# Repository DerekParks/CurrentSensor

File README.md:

Read a Non-invasive AC Current Sensor (SCT-013) hooked up to a adc (ADS1115) and a ESP-01. Then emit to mqtt. 
Saves wifi and mqtt creds to SPIFFS.
If wifi creds not found will go into AP mode.

# Links
https://www.savjee.be/2019/07/Home-Energy-Monitor-ESP32-CT-Sensor-Emonlib/

https://learn.openenergymonitor.org/electricity-monitoring/ct-sensors/how-to-build-an-arduino-energy-monitor-measuring-current-only?redirected=true

https://github.com/openenergymonitor/EmonLib

https://cdn-learn.adafruit.com/downloads/pdf/adafruit-4-channel-adc-breakouts.pdf

https://forum.mysensors.org/topic/4887/sct-013-030-to-measure-watt/3

http://www.sensingthecity.com/creating-a-non-invasive-current-sensor/

# Web server
https://github.com/Jorgen-VikingGod/ESP8266-WiFi-Relay-Async

# Board desgin links

## ESP01 I2C
https://simple-circuit.com/esp8266-esp-01-i2c-lcd/

## RST and FLASH switch
https://www.instructables.com/id/FTDI-ESP8266-Definitive-Wiring/

https://www.allaboutcircuits.com/projects/breadboard-and-program-an-esp-01-circuit-with-the-arduino-ide/

https://www.allaboutcircuits.com/projects/flashing-the-ESP-01-firmware-to-SDK-v2.0.0-is-easier-now/

https://taillieu.info/index.php/articles/category-list/204-esp8266-developer-board-for-the-esp-01-and-esp-12

## Used for FTDI:
https://github.com/ppelleti/avr-arduino-kicad

https://www.forward.com.au/pfod/ESP8266/GPIOpins/ESP8266_01_pin_magic.html

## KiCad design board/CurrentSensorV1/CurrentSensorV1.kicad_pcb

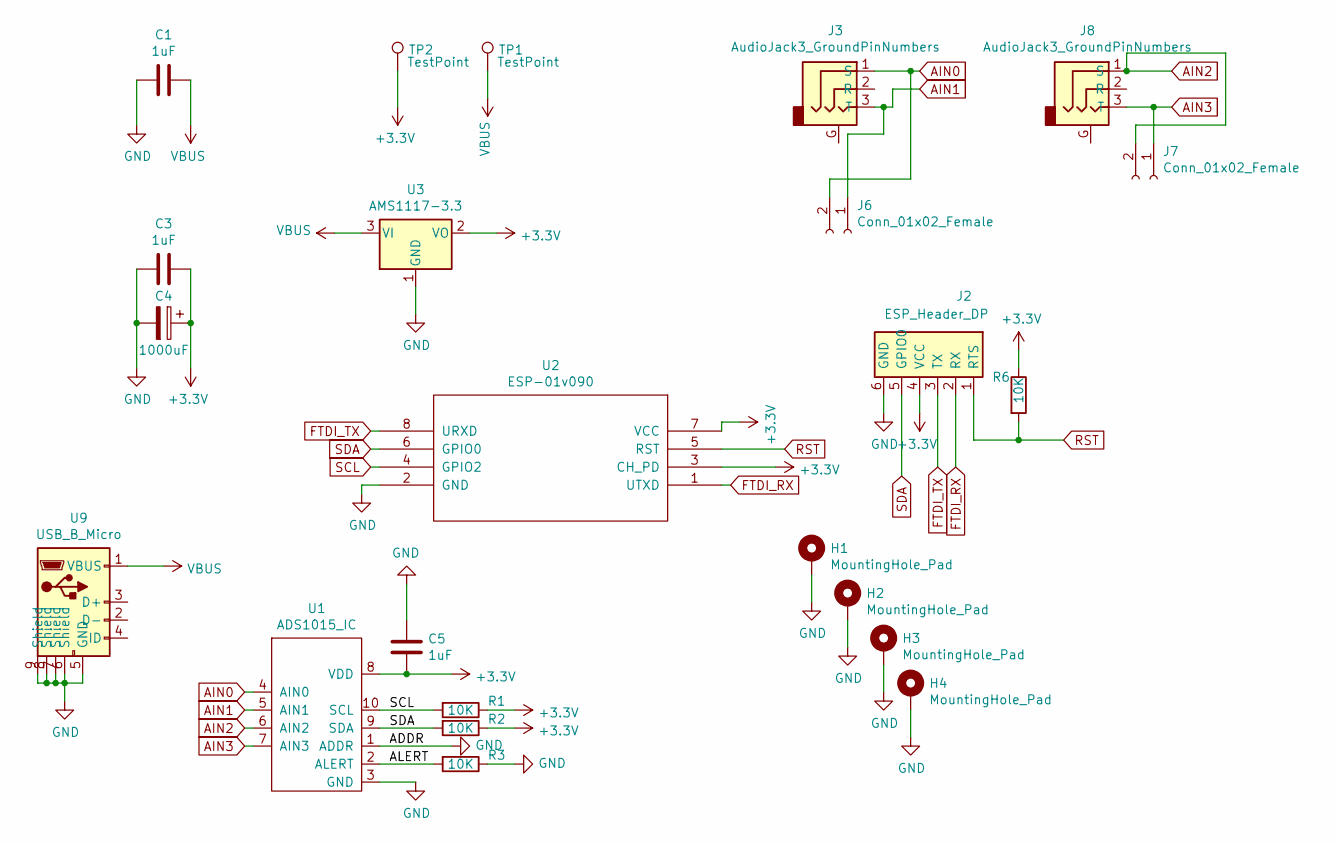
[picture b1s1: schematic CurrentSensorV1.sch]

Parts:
C1, C3, C5: 1uF; C_0402_1005Metric; LCSC C52923
C4: 1000uF; C_Elec_8x10.2; LCSC C99833
H1, H2, H3, H4: MountingHole_Pad; MountingHole_2.5mm_Pad
J2: ESP_Header_DP; FTDI_Header
J3, J8: AudioJack3_GroundPinNumbers; Tayda_3.5mm_stereo_TRS_jack_A-853
J6, J7: Conn_01x02_Female; PinHeader_1x02_P2.54mm_Vertical
R1, R2, R3, R6: 10K; R_0603_1608Metric; LCSC C23192
TP1, TP2: TestPoint; PinSocket_1x01_P2.54mm_Vertical
U1: ADS1015_IC; VSSOP-10_3x3mm_P0.5mm; LCSC C193969
U2: ESP-01v090; ESP-01
U3: AMS1117-3.3; SOT-223-3_TabPin2; LCSC C6186
U9: USB_B_Micro; USB_MICRO_M5SS_DP; LCSC C404968

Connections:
+3V3: C3.1, C4.1, C5.2, J2.4 (VCC), R1.1, R2.1, R6.1, TP2.1, U1.8 (VDD), U2.3 (CH_PD), U2.7 (VCC), U3.2 (VO)
/ALERT: R3.2, U1.2 (ALERT)
AIN0: J3.1 (S), J6.2, U1.4 (AIN0)
AIN1: J3.3 (T), J6.1, U1.5 (AIN1)
AIN2: J7.2, J8.1 (S), U1.6 (AIN2)
AIN3: J7.1, J8.3 (T), U1.7 (AIN3)
FTDI_RX: J2.2 (RX), U2.1 (UTXD)
FTDI_TX: J2.3 (TX), U2.8 (URXD)
GND: C1.2, C3.2, C4.2, C5.1, H1.1, H2.1, H3.1, H4.1, J2.6 (GND), R3.1, U1.1 (ADDR), U1.3 (GND), U2.2 (GND), U3.1 (GND), U9.5 (GND), U9.6 (Shield), U9.7 (Shield), U9.8 (Shield), U9.9 (Shield)
RST: J2.1 (RTS), R6.2, U2.5 (RST)
SCL: R1.2, U1.10 (SCL), U2.4 (GPIO2)
SDA: J2.5 (GPIO0), R2.2, U1.9 (SDA), U2.6 (GPIO0)
VBUS: C1.1, TP1.1, U3.3 (VI), U9.1 (VBUS)

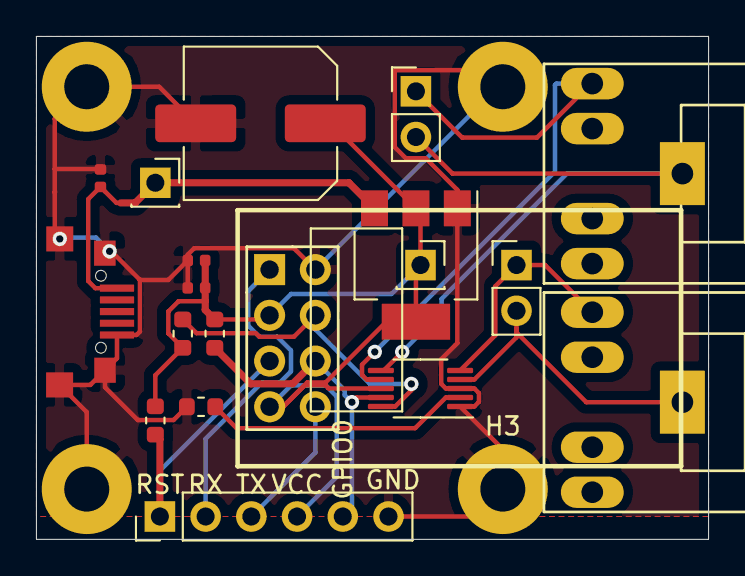
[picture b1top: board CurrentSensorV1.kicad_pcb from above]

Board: 2 copper layers, 37.3 x 27.9 mm, 23 parts (0 on the bottom side), 13 nets.

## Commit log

2021-01-02 Inital Commit
2021-01-02 Docs
2021-01-03 Make calibration factor configurable
2021-01-10 Add Thresholding option and make publish topic configurable
2021-01-20 Fix non call of load cal factor from EEPROM
2021-01-21 Bug Fixes
2021-05-12 Starting v4
2021-05-14 Working on V4
2021-05-14 adding assembly script
